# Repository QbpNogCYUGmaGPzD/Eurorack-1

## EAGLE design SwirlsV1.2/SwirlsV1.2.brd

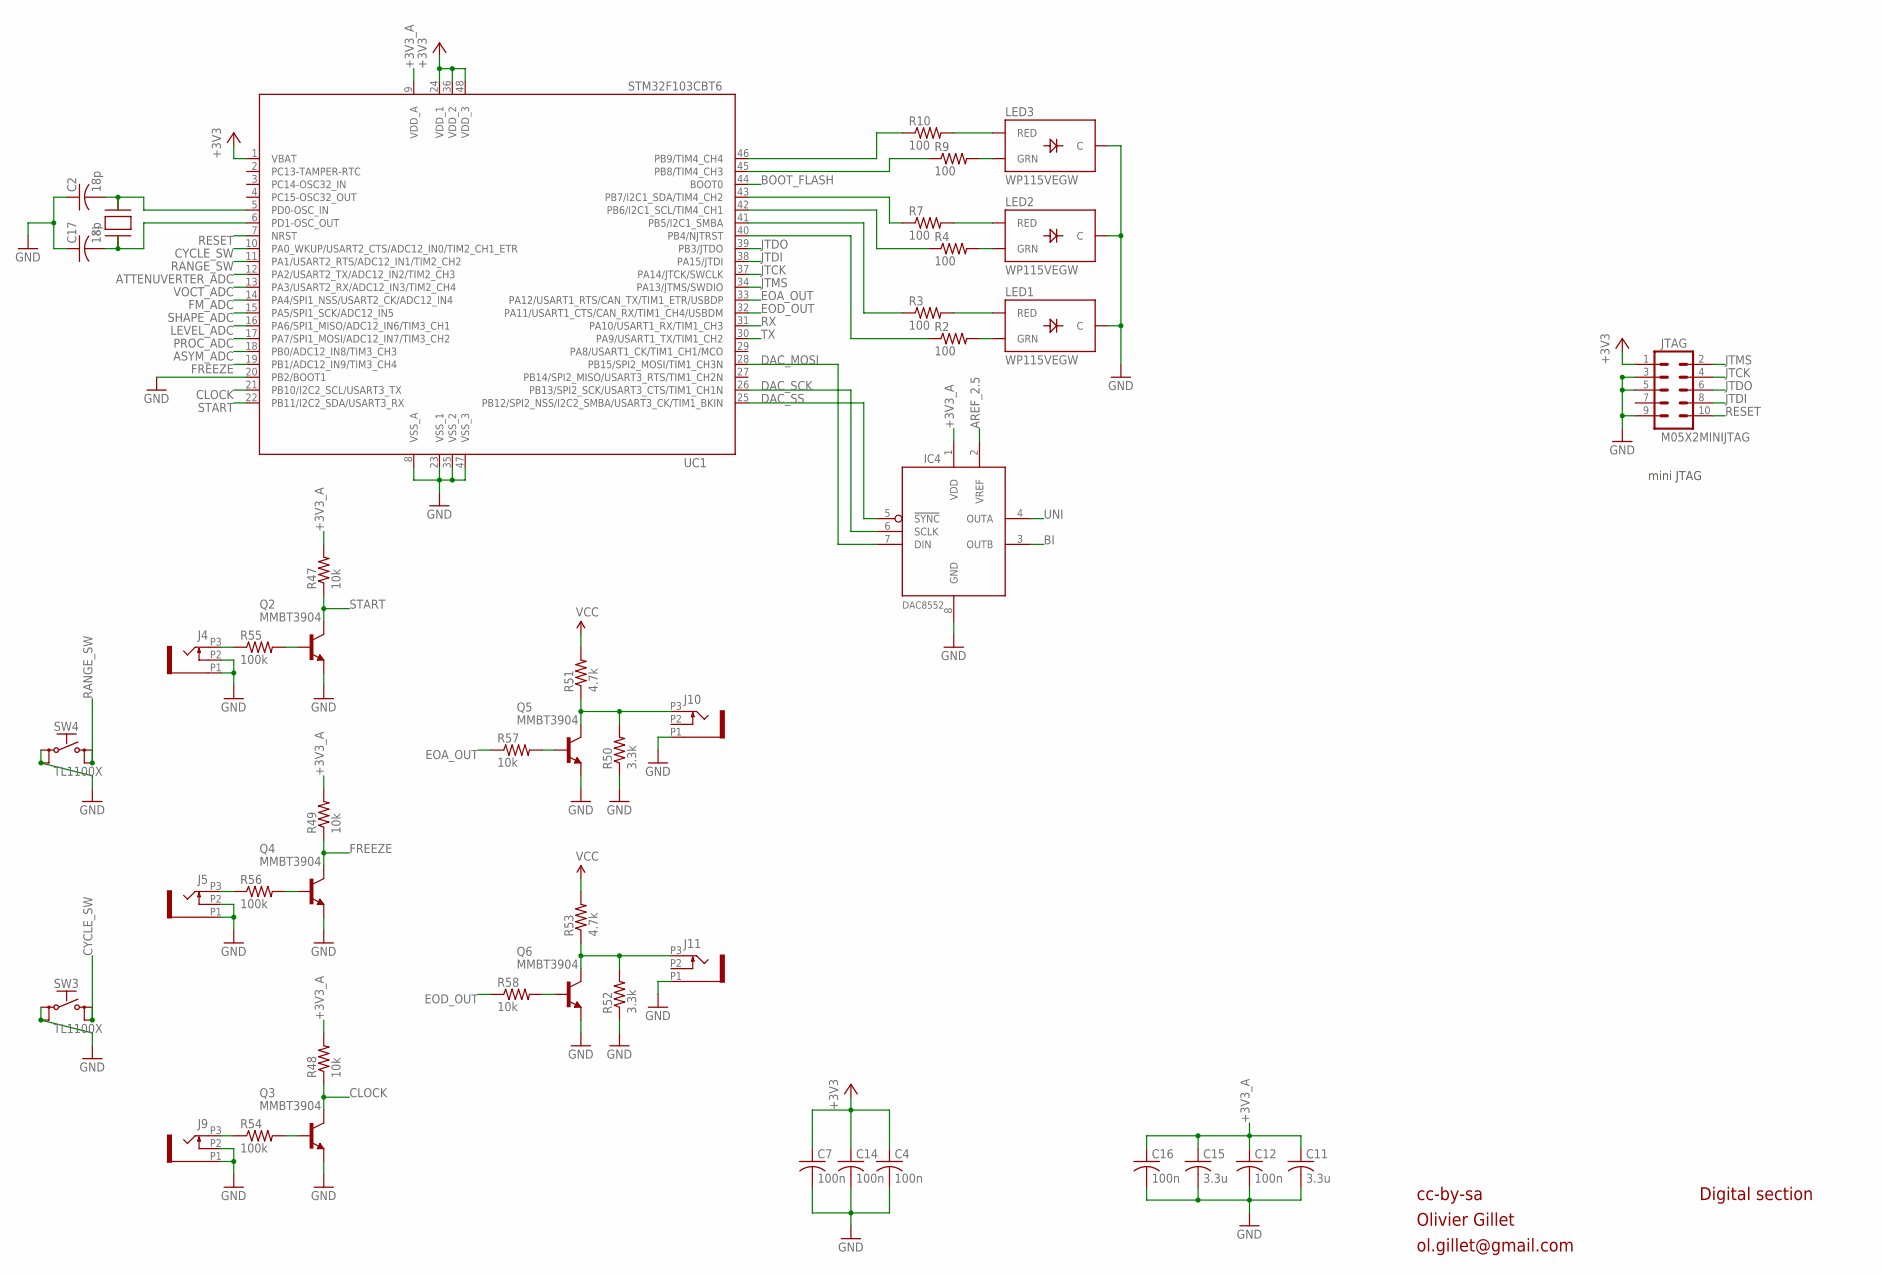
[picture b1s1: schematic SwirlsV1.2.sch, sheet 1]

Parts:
C2, C17: 18p; C0603
C4, C7, C12, C14, C16: 100n; C0603
C11, C15: 3.3u; C0603
IC4: DAC8552; MSOP-8
J4, J5, J9, J10, J11: PJ301_GUI6; OG-PJ301_VARIATIONS_WQP_PJ_301M6
JTAG: M05X2MINIJTAG; 2X5-1.27
LED1, LED2, LED3: WP115VEGW; LED-BICOLOR-THROUGHHOLE
Q2, Q3, Q4, Q5, Q6: MMBT3904; SOT23-BEC
R2, R3, R4, R7, R9, R10: 100; R0603
R47, R48, R49, R57, R58: 10k; R0603
R50, R52: 3.3k; R0603
R51, R53: 4.7k; R0603
R54, R55, R56: 100k; R0603
SW3, SW4: TL1100X
UC1: STM32F103CBT6; LQFP48
X1: XTALNX5032; NX5032

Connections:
+3V3: C4.1, C7.1, C14.1, JTAG.1, UC1.1 (VBAT), UC1.24 (VDD_1), UC1.36 (VDD_2), UC1.48 (VDD_3); also elsewhere on the board
+3V3_A: C11.1, C12.1, C15.1, C16.1, IC4.1 (VDD), R47.2, R48.2, R49.2, UC1.9 (VDD_A); also elsewhere on the board
AREF_2.5: IC4.2 (VREF); also elsewhere on the board
ASYM_ADC: UC1.18 (PB0/ADC12_IN8/TIM3_CH3); also elsewhere on the board
ATTENUVERTER_ADC: UC1.12 (PA2/USART2_TX/ADC12_IN2/TIM2_CH3); also elsewhere on the board
BI: IC4.3 (OUTB); also elsewhere on the board
BOOT_FLASH: UC1.44 (BOOT0)
CLOCK: Q3.C, R48.1, UC1.21 (PB10/I2C2_SCL/USART3_TX)
CYCLE_SW: SW3.3 (S), SW3.4 (S1), UC1.10 (PA0_WKUP/USART2_CTS/ADC12_IN0/TIM2_CH1_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)
DAC_MOSI: IC4.7 (DIN), UC1.28 (PB15/SPI2_MOSI/TIM1_CH3N)
DAC_SCK: IC4.6 (SCLK), UC1.26 (PB13/SPI2_SCK/USART3_CTS/TIM1_CH1N)
DAC_SS: IC4.5 (!SYNC), UC1.25 (PB12/SPI2_NSS/I2C2_SMBA/USART3_CK/TIM1_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)
EOA_OUT: R57.1, UC1.33 (PA12/USART1_RTS/CAN_TX/TIM1_ETR/USBDP)
EOD_OUT: R58.1, UC1.32 (PA11/USART1_CTS/CAN_RX/TIM1_CH4/USBDM)
FM_ADC: UC1.14 (PA4/SPI1_NSS/USART2_CK/ADC12_IN4); also elsewhere on the board
FREEZE: Q4.C, R49.1, UC1.19 (PB1/ADC12_IN9/TIM3_CH4)
GND: C2.1, C4.2, C7.2, C11.2, C12.2, C14.2, C15.2, C16.2, C17.1, IC4.8 (GND), J4.P1 (1), J4.P2 (2), J5.P1 (1), J5.P2 (2), J9.P1 (1), J9.P2 (2), J10.P1 (1), J11.P1 (1), JTAG.3, JTAG.5, JTAG.9, LED1.2 (C), LED2.2 (C), LED3.2 (C), Q2.E, Q3.E, Q4.E, Q5.E, Q6.E, R50.1, R52.1, SW3.1, SW3.2 (P1), SW4.1, SW4.2 (P1), UC1.8 (VSS_A), UC1.20 (PB2/BOOT1), UC1.23 (VSS_1), UC1.35 (VSS_2), UC1.47 (VSS_3); also elsewhere on the board
JTCK: JTAG.4, UC1.37 (PA14/JTCK/SWCLK)
JTDI: JTAG.8, UC1.38 (PA15/JTDI)
JTDO: JTAG.6, UC1.39 (PB3/JTDO)
JTMS: JTAG.2, UC1.34 (PA13/JTMS/SWDIO)
LEVEL_ADC: UC1.16 (PA6/SPI1_MISO/ADC12_IN6/TIM3_CH1); also elsewhere on the board
unnamed: C2.2, UC1.5 (PD0-OSC_IN), X1.P$2
unnamed: C17.2, UC1.6 (PD1-OSC_OUT), X1.P$1
unnamed: J5.P3 (3), R56.1
unnamed: Q4.B, R56.2
unnamed: J9.P3 (3), R54.1
unnamed: Q3.B, R54.2
unnamed: Q6.B, R58.2
unnamed: J11.P3 (3), Q6.C, R52.2, R53.1
unnamed: LED3.3 (RED), R10.2
unnamed: LED3.1 (GRN), R9.2
unnamed: LED2.3 (RED), R7.2
unnamed: LED2.1 (GRN), R4.2
unnamed: LED1.3 (RED), R3.2
unnamed: LED1.1 (GRN), R2.2
unnamed: R10.1, UC1.46 (PB9/TIM4_CH4)
unnamed: R9.1, UC1.45 (PB8/TIM4_CH3)
unnamed: R7.1, UC1.43 (PB7/I2C1_SDA/TIM4_CH2)
unnamed: R4.1, UC1.42 (PB6/I2C1_SCL/TIM4_CH1)
unnamed: R3.1, UC1.41 (PB5/I2C1_SMBA)
unnamed: R2.1, UC1.40 (PB4/NJTRST)
unnamed: J10.P3 (3), Q5.C, R50.2, R51.1
unnamed: Q5.B, R57.2
unnamed: J4.P3 (3), R55.1
unnamed: Q2.B, R55.2
PROC_ADC: UC1.17 (PA7/SPI1_MOSI/ADC12_IN7/TIM3_CH2); also elsewhere on the board
RANGE_SW: SW4.3 (S), SW4.4 (S1), UC1.11 (PA1/USART2_RTS/ADC12_IN1/TIM2_CH2)
RESET: JTAG.10, UC1.7 (NRST)
RX: UC1.31 (PA10/USART1_RX/TIM1_CH3)
SHAPE_ADC: UC1.15 (PA5/SPI1_SCK/ADC12_IN5); also elsewhere on the board
START: Q2.C, R47.1, UC1.22 (PB11/I2C2_SDA/USART3_RX)
TX: UC1.30 (PA9/USART1_TX/TIM1_CH2)
UNI: IC4.4 (OUTA); also elsewhere on the board
VCC: R51.2, R53.2; also elsewhere on the board
VOCT_ADC: UC1.13 (PA3/USART2_RX/ADC12_IN3/TIM2_CH4); also elsewhere on the board

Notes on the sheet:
cc-by-sa
Olivier Gillet
ol.gillet@gmail.com
Digital section
mini JTAG

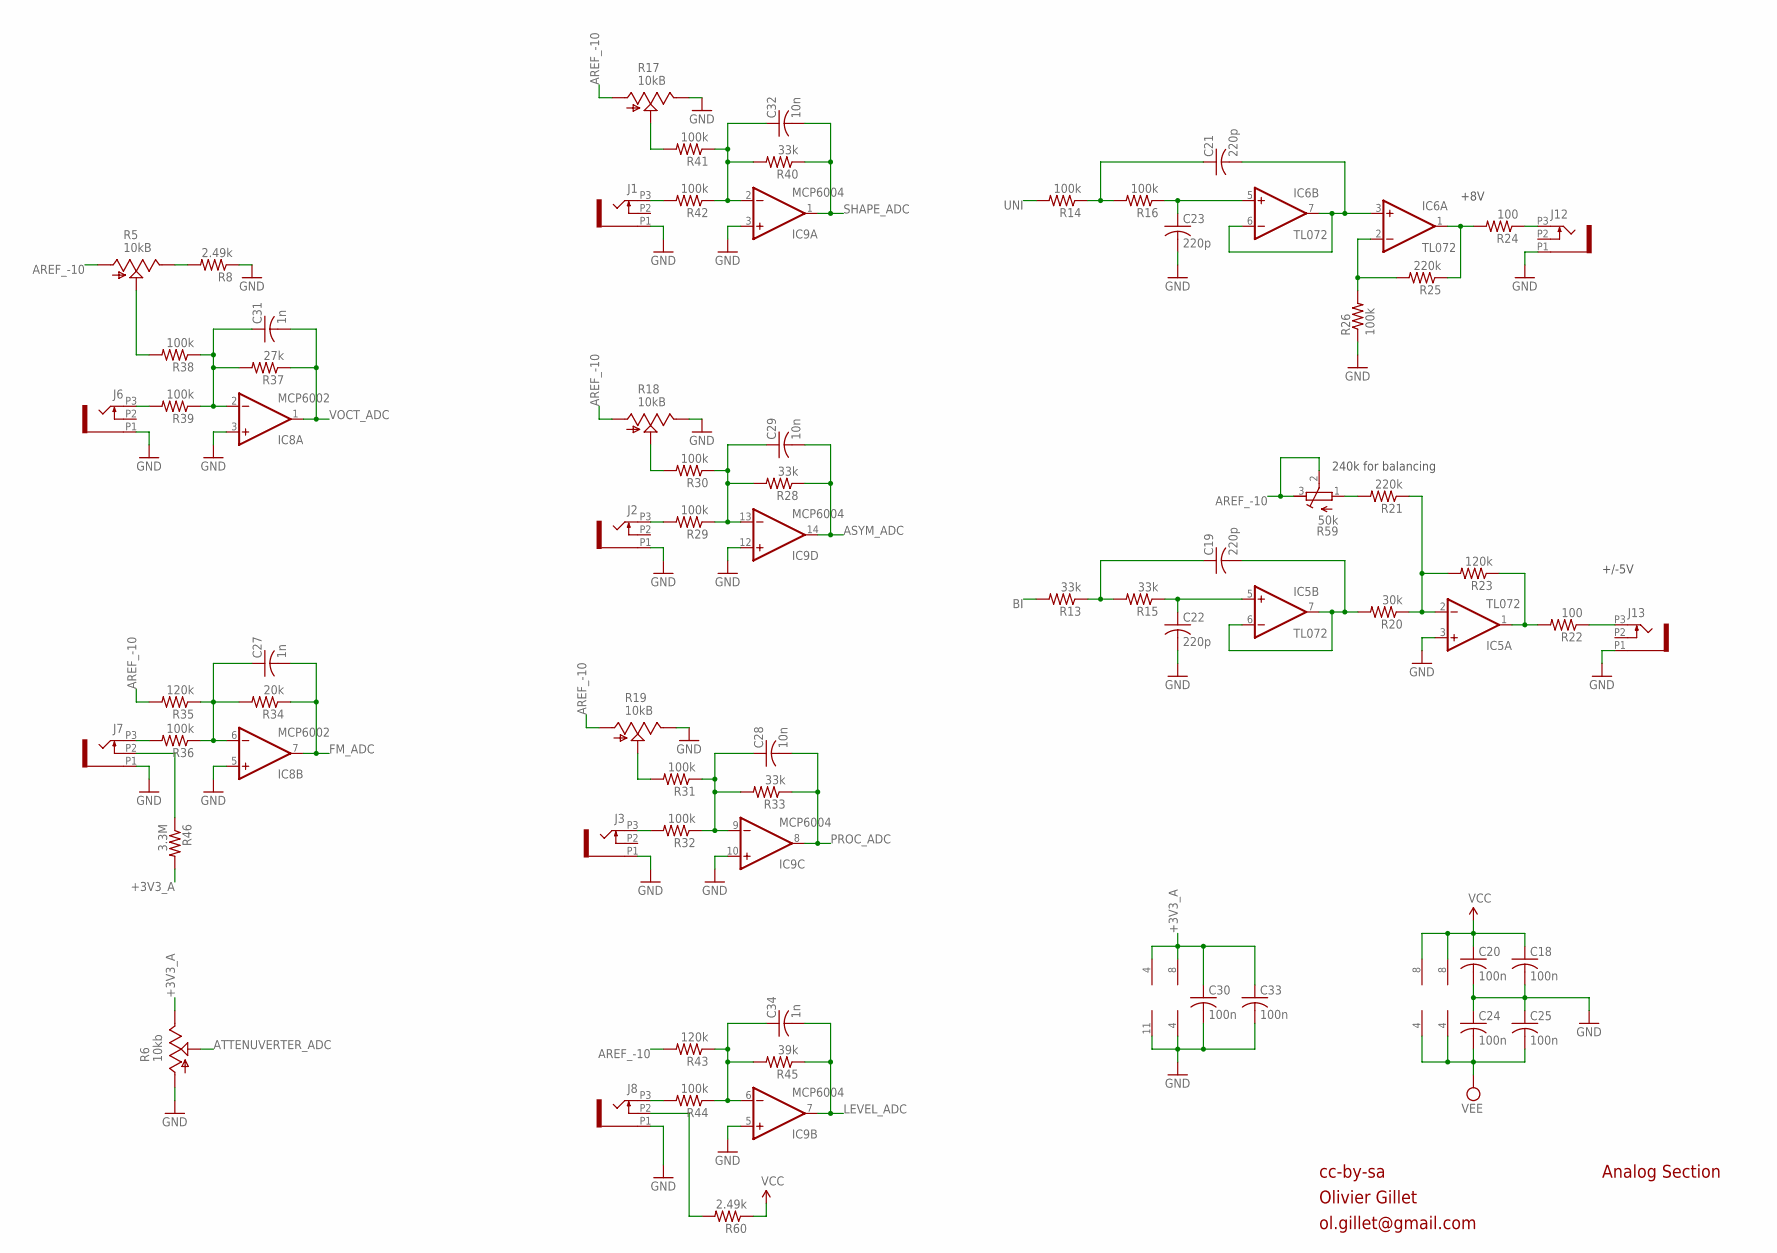
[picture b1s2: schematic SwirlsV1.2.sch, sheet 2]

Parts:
C18, C20, C24, C25, C30, C33: 100n; C0603
C19, C21, C22, C23: 220p; C0603
C27, C31, C34: 1n; C0603
C28, C29, C32: 10n; C0603
IC5, IC6: TL072; TSSOP-8
IC8: MCP6002; SO08
IC9: MCP6004; TSSOP14
J1, J2, J3, J6, J7, J8, J12, J13: PJ301_GUI6; OG-PJ301_VARIATIONS_WQP_PJ_301M6
R5: 10kB; ALPS_POT_VERTICAL_PS
R6: 10kb; TALLTRIMMER
R8: 2.49k; R0603
R13, R15, R28, R33, R40: 33k; R0603
R14, R16, R26, R29, R30, R31, R32, R36, R38, R39, R41, R42, R44: 100k; R0603
R17, R18, R19: 10kB; TALLTRIMMER
R20: 30k; R0603
R21, R25: 220k; R0603
R22, R24: 100; R0603
R23, R35, R43: 120k; R0603
R34: 20k; R0603
R37: 27k; R0603
R45: 39k; R0603
R46: 3.3M; R0603
R59: 50k; RTRIM3296W
R60: 2.49k; R0805

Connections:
+3V3_A: C30.1, C33.1, IC8.8 (V+), IC9.4 (V+), R6.P$1 (E), R46.2; also elsewhere on the board
AREF_-10: R5.P$3 (A), R17.P$3 (A), R18.P$3 (A), R19.P$3 (A), R35.2, R43.2, R59.2 (S), R59.3 (E); also elsewhere on the board
ASYM_ADC: C29.2, IC9.14 (OUT), R28.1; also elsewhere on the board
ATTENUVERTER_ADC: R6.P$2 (S); also elsewhere on the board
BI: R13.2; also elsewhere on the board
BI_OUT: IC5.1 (OUT), R22.2, R23.1
FM_ADC: C27.2, IC8.7 (OUT), R34.1; also elsewhere on the board
F_CV: IC5.2 (-IN), R20.1, R21.1, R23.2
GND: C18.2, C20.2, C22.2, C23.2, C24.1, C25.1, C30.2, C33.2, IC5.3 (+IN), IC8.3 (+IN), IC8.4 (V-), IC8.5 (+IN), IC9.3 (+IN), IC9.5 (+IN), IC9.10 (+IN), IC9.11 (V-), IC9.12 (+IN), J1.P1 (1), J2.P1 (1), J3.P1 (1), J6.P1 (1), J7.P1 (1), J8.P1 (1), J12.P1 (1), J13.P1 (1), R6.P$3 (A), R8.1, R17.P$1 (E), R18.P$1 (E), R19.P$1 (E), R26.1; also elsewhere on the board
LEVEL_ADC: C34.2, IC9.7 (OUT), R45.1; also elsewhere on the board
unnamed: J1.P3 (3), R42.2
unnamed: C32.1, IC9.2 (-IN), R40.2, R41.1, R42.1
unnamed: R17.P$2 (S), R41.2
unnamed: J2.P3 (3), R29.2
unnamed: C29.1, IC9.13 (-IN), R28.2, R29.1, R30.1
unnamed: J7.P2 (2), R46.1
unnamed: R18.P$2 (S), R30.2
unnamed: J3.P3 (3), R32.2
unnamed: C28.1, IC9.9 (-IN), R31.1, R32.1, R33.2
unnamed: R19.P$2 (S), R31.2
unnamed: J8.P3 (3), R44.2
unnamed: C34.1, IC9.6 (-IN), R43.1, R44.1, R45.2
unnamed: J6.P3 (3), R39.2
unnamed: C31.1, IC8.2 (-IN), R37.2, R38.1, R39.1
unnamed: R5.P$2 (S), R38.2
unnamed: J13.P3 (3), R22.1
unnamed: R5.P$1 (E), R8.2
unnamed: J7.P3 (3), R36.2
unnamed: C27.1, IC8.6 (-IN), R34.2, R35.1, R36.1
unnamed: R21.2, R59.1 (A)
unnamed: IC6.2 (-IN), R25.2, R26.2
unnamed: C19.2, IC5.6 (-IN), IC5.7 (OUT), R20.2
unnamed: C22.1, IC5.5 (+IN), R15.1
unnamed: C19.1, R13.1, R15.2
unnamed: IC6.1 (OUT), R24.2, R25.1
unnamed: J8.P2 (2), R60.2
unnamed: C21.2, IC6.3 (+IN), IC6.6 (-IN), IC6.7 (OUT)
unnamed: C23.1, IC6.5 (+IN), R16.1
unnamed: C21.1, R14.1, R16.2
PROC_ADC: C28.2, IC9.8 (OUT), R33.1; also elsewhere on the board
SHAPE_ADC: C32.2, IC9.1 (OUT), R40.1; also elsewhere on the board
UNI: R14.2; also elsewhere on the board
UNI_OUT: J12.P3 (3), R24.1
VCC: C18.1, C20.1, IC5.8 (V+), IC6.8 (V+), R60.1; also elsewhere on the board
VEE: C24.2, C25.2, IC5.4 (V-), IC6.4 (V-); also elsewhere on the board
VOCT_ADC: C31.2, IC8.1 (OUT), R37.1; also elsewhere on the board

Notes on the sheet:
cc-by-sa
Olivier Gillet
ol.gillet@gmail.com
Analog Section
+8V
+/-5V
240k for balancing

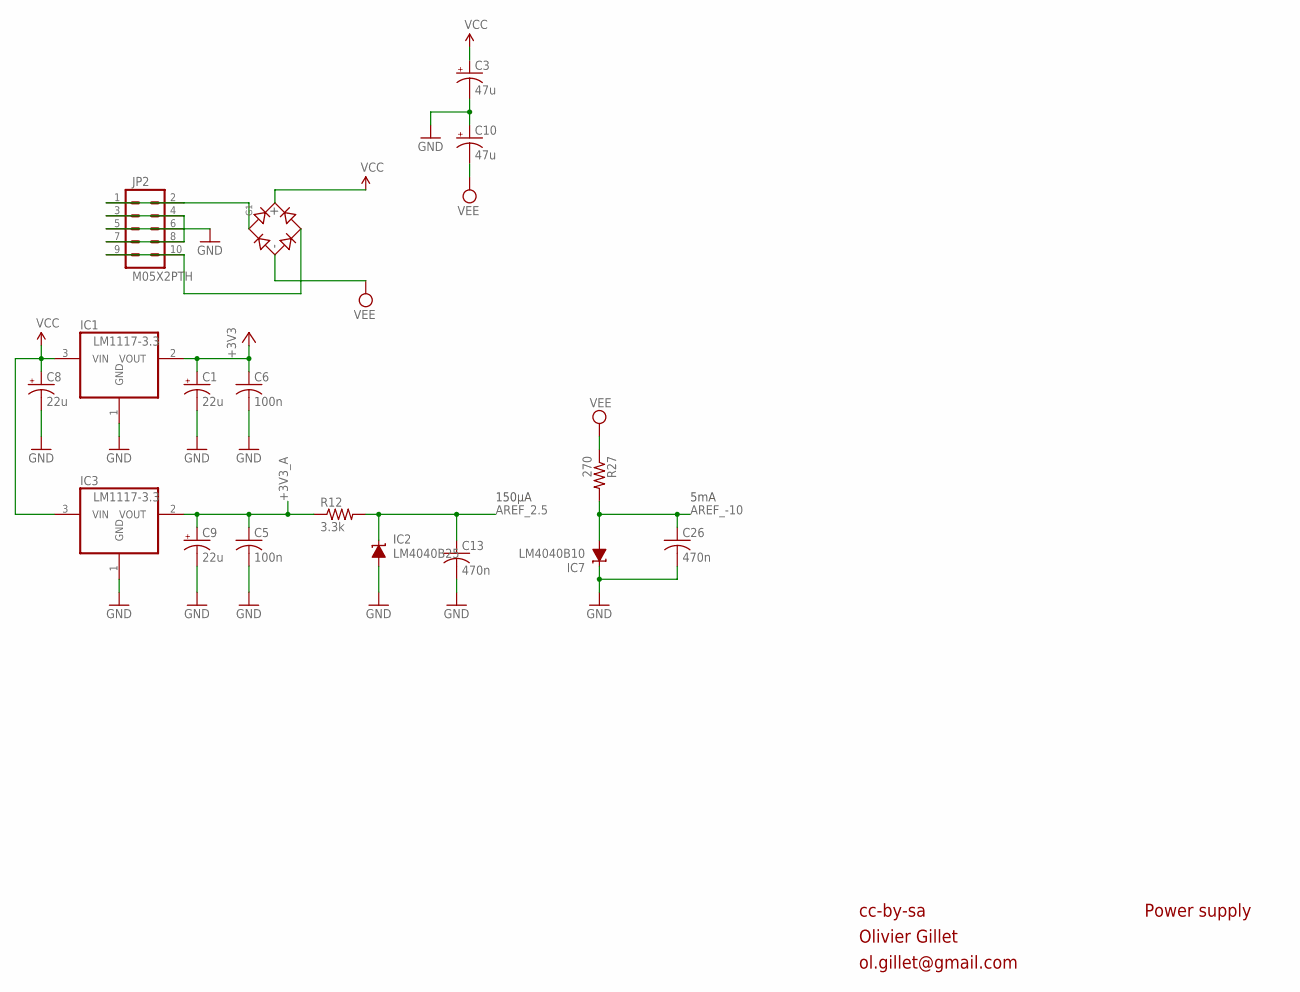
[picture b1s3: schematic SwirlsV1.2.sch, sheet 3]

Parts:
C1, C8, C9: 22u; PANASONIC_C
C3, C10: 47u; PANASONIC_C
C5, C6: 100n; C0603
C13, C26: 470n; C0603
G1: BRIDGERECTIFIER; SOIC-4
IC1, IC3: LM1117-3.3; SOT223
IC2: LM4040B25; DBZ_R-PDSO-G3
IC7: LM4040B10; DBZ_R-PDSO-G3
JP2: M05X2PTH; AVR_ICSP
R12: 3.3k; R0603
R27: 270; R0603

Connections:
+3V3: C1.+, C6.1, IC1.2 (VOUT); also elsewhere on the board
+3V3_A: C5.1, C9.+, IC3.2 (VOUT), R12.1; also elsewhere on the board
AREF_2.5: C13.1, IC2.1 (C), R12.2; also elsewhere on the board
AREF_-10: C26.1, IC7.2 (A), R27.2; also elsewhere on the board
GND: C1.-, C3.-, C5.2, C6.2, C8.-, C9.-, C10.+, C13.2, C26.2, IC1.1 (GND), IC2.2 (A), IC3.1 (GND), IC7.1 (C), JP2.3, JP2.4, JP2.5, JP2.6, JP2.7, JP2.8; also elsewhere on the board
unnamed: G1.~1 (AC1), JP2.1, JP2.2
unnamed: G1.~2 (AC2), JP2.9, JP2.10
VCC: C3.+, C8.+, G1.+, IC1.3 (VIN), IC3.3 (VIN); also elsewhere on the board
VEE: C10.-, G1.-, R27.1; also elsewhere on the board

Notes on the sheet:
cc-by-sa
Olivier Gillet
ol.gillet@gmail.com
Power supply
5mA
150µA

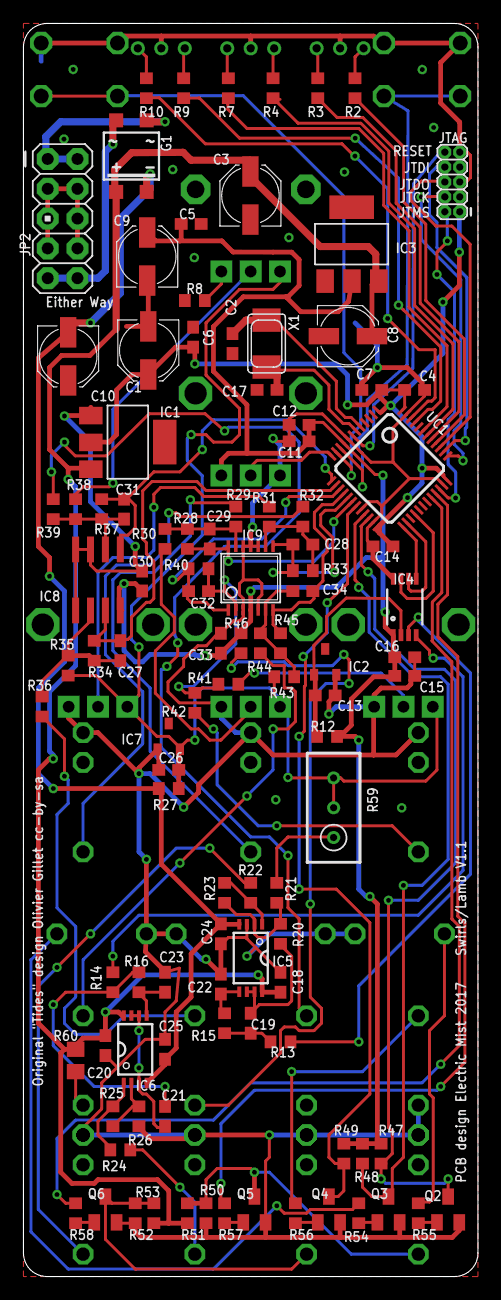
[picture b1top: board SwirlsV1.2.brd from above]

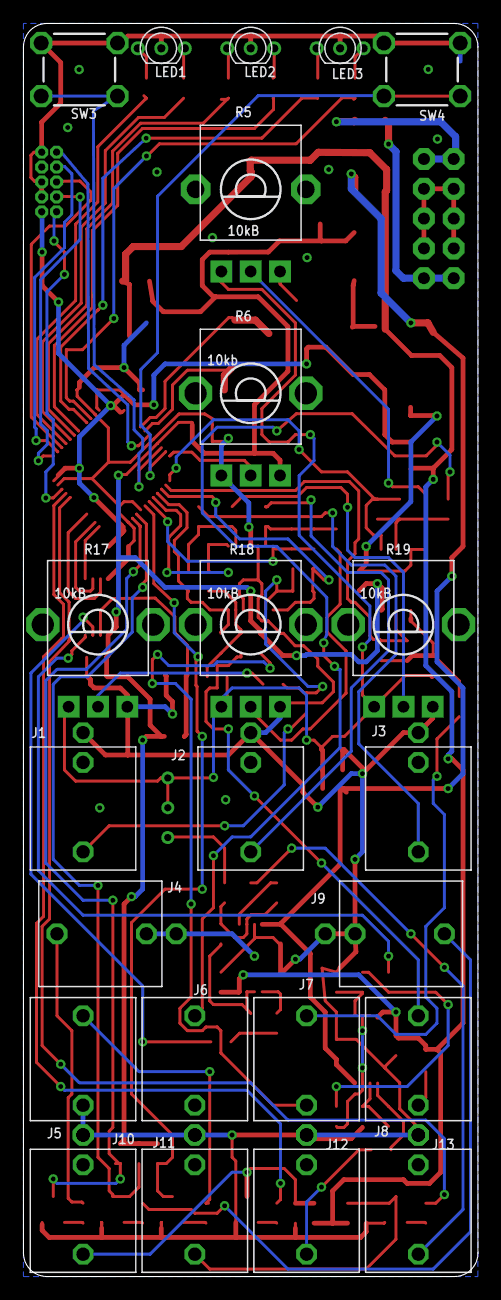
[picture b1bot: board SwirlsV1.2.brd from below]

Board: 2 copper layers, 38.7 x 106.8 mm, 129 parts (23 on the bottom side), 89 nets.

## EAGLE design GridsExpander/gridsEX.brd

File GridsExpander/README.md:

# Grids Midi In expander with 1x4 Midi Through Circuit

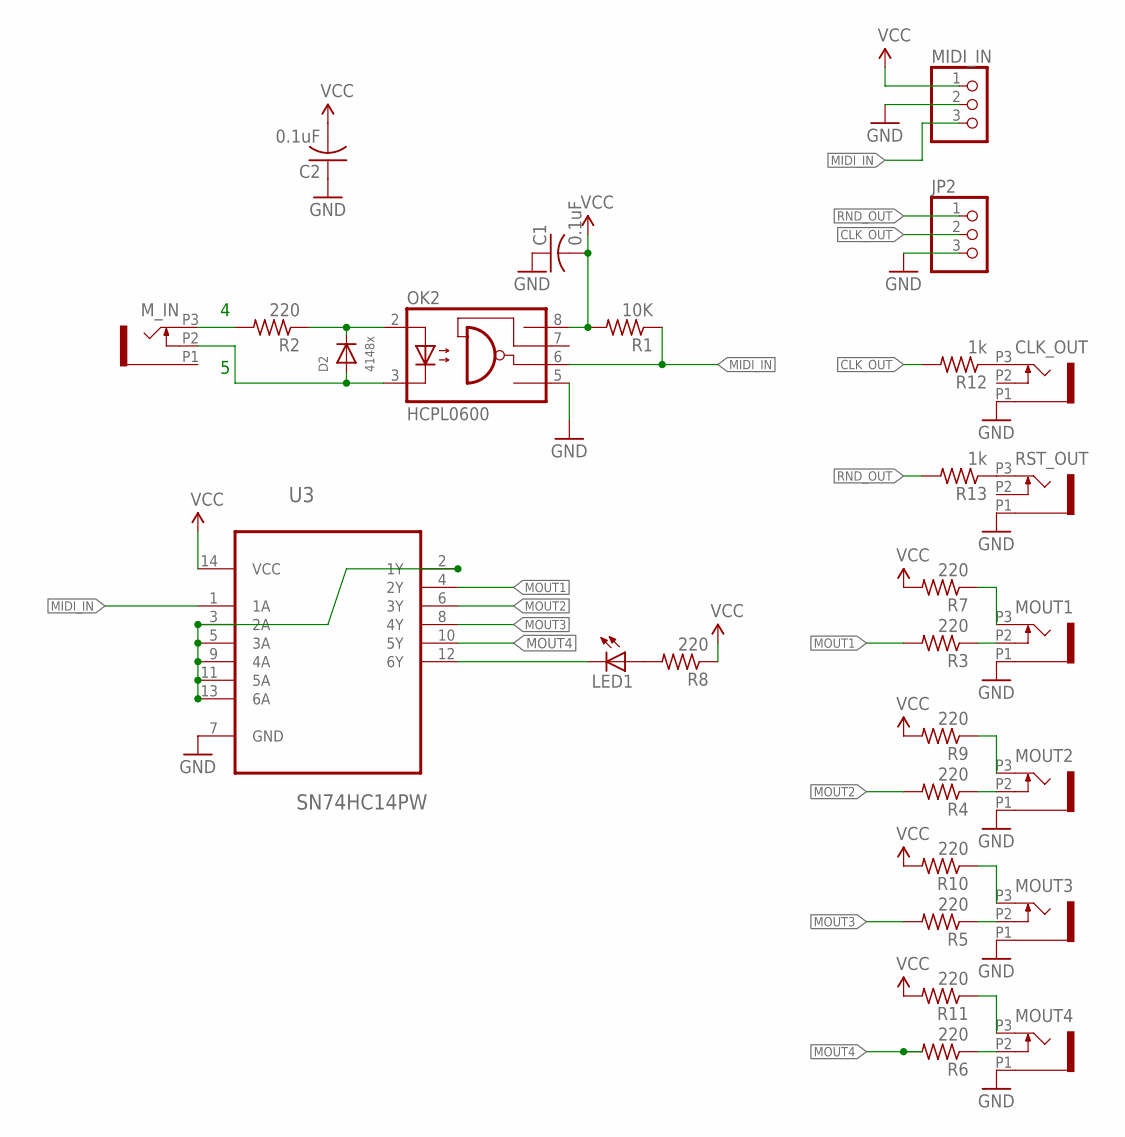
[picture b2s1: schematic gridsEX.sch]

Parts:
C1, C2: 0.1uF; RCL_C0603K
CLK_OUT: PJ301_GUI6; OG-PJ301_VARIATIONS_WQP_PJ_301M6
D2: 4148x; SOD-123
JP2: PINHD-1X3; 1X03
LED1: LED3MM
MIDI_IN: PINHD-1X3; 1X03
MOUT1, MOUT2, MOUT3, MOUT4: PJ301_GUI6; OG-PJ301_VARIATIONS_WQP_PJ_301M6
M_IN: PJ301_GUI6; OG-PJ301_VARIATIONS_WQP_PJ_301M6
OK2: HCPL0600; SOIC08
R1: 10K; RCL_R0603
R2, R3, R4, R5, R6, R7, R8, R9, R10, R11: 220; RCL_R0603
R12, R13: 1k; RCL_R0603
RST_OUT: PJ301_GUI6; OG-PJ301_VARIATIONS_WQP_PJ_301M6
U3: SN74HC14PW; SOP65P640X120-14N

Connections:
CLK_OUT: JP2.2, R12.2
GND: C1.1, C2.1, CLK_OUT.P1 (1), JP2.3, MIDI_IN.2, MOUT1.P1 (1), MOUT2.P1 (1), MOUT3.P1 (1), MOUT4.P1 (1), OK2.5 (GND), RST_OUT.P1 (1), U3.7 (GND)
MIDI_IN: MIDI_IN.3, OK2.6 (VO), R1.1, U3.1 (1A)
MOUT1: R3.2, U3.4 (2Y)
MOUT2: R4.2, U3.6 (3Y)
MOUT3: R5.2, U3.8 (4Y)
MOUT4: R6.2, U3.10 (5Y)
unnamed: LED1.K (C), U3.12 (6Y)
unnamed: D2.C, OK2.2 (A), R2.1
unnamed: M_IN.P3 (3), R2.2
unnamed: D2.A, M_IN.P2 (2), OK2.3 (C)
unnamed: LED1.A, R8.2
unnamed: U3.2 (1Y), U3.3 (2A), U3.5 (3A), U3.9 (4A), U3.11 (5A), U3.13 (6A)
unnamed: MOUT1.P2 (2), R3.1
unnamed: MOUT1.P3 (3), R7.1
unnamed: MOUT2.P3 (3), R9.1
unnamed: MOUT3.P3 (3), R10.1
unnamed: MOUT4.P3 (3), R11.1
unnamed: MOUT2.P2 (2), R4.1
unnamed: MOUT3.P2 (2), R5.1
unnamed: MOUT4.P2 (2), R6.1
unnamed: CLK_OUT.P3 (3), R12.1
unnamed: R13.1, RST_OUT.P3 (3)
RND_OUT: JP2.1, R13.2
VCC: C1.2, C2.2, MIDI_IN.1, OK2.8 (VCC), R1.2, R7.2, R8.1, R9.2, R10.2, R11.2, U3.14 (VCC)

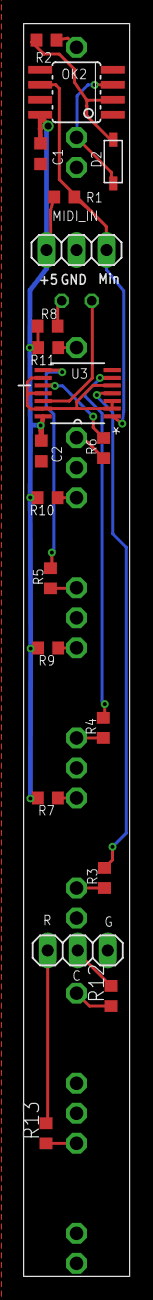
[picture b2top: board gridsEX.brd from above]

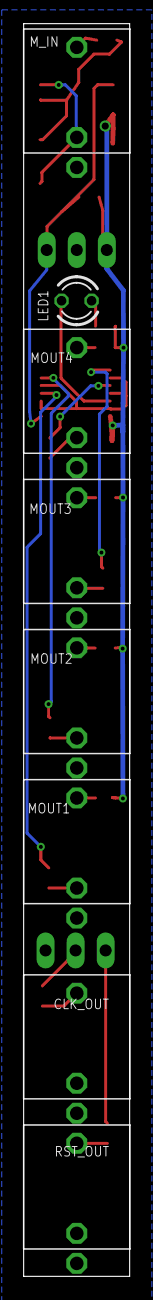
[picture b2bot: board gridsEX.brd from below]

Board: 2 copper layers, 9.0 x 106.0 mm, 28 parts (8 on the bottom side), 25 nets.

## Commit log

2018-02-24 GridEX
2018-03-08 Added BOM
2018-03-08 typos
2018-03-08 more typos
2018-03-08 organize
2018-04-10 fixed
2019-04-06 liscense stuff
2019-04-06 More License stuff
2019-04-06 KiCad files
2019-04-08 CleanUp
2019-04-08 Personalize

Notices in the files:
SwirlsV1.2/SwirlsV1.2.brd:
Original "Tides" design Olivier Gillet cc-by-sa
parts and their libraries:
switch-e-switch: Copyright (C) 2010, Bob Starr
microbuilder: This work is placed in the public domain, and may be freely used for commercial and non-commercial work with the following conditions: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
